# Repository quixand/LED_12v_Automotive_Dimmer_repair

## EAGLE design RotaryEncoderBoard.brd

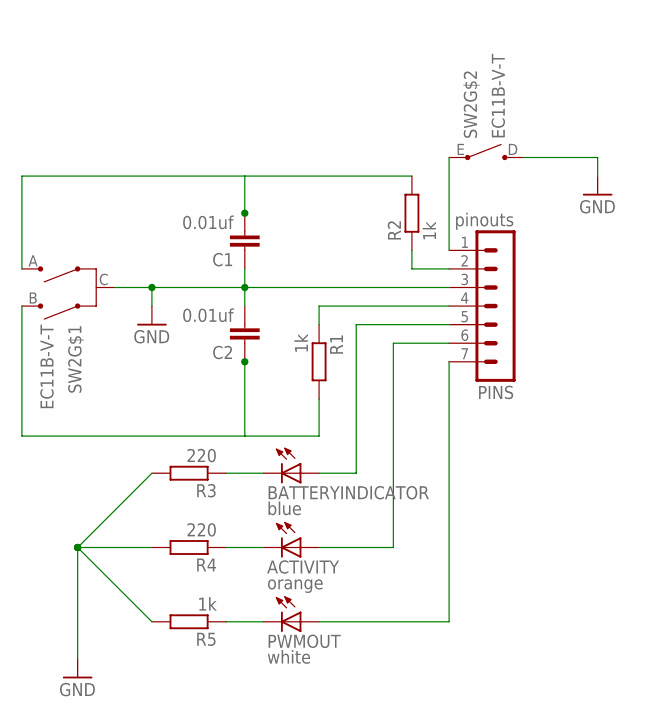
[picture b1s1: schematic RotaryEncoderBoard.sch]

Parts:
ACTIVITY: orange; LED-1206
BATTERYINDICATOR: blue; LED-1206
C1, C2: 0.01uf; C2.5-3
PINS: pinouts; MA07-1
PWMOUT: white; LED-1206
R1, R2, R5: 1k; 0204/7
R3, R4: 220; 0204/7
SW2: EC11B-V-T; EC11B-V

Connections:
GND: C1.1, C2.2, PINS.3, R3.2, R4.2, R5.2, SW2.C, SW2.D
unnamed: PINS.2, R2.1
unnamed: C1.2, R2.2, SW2.A
unnamed: C2.1, R1.2, SW2.B
unnamed: PINS.4, R1.1
unnamed: PINS.7, PWMOUT.A
unnamed: ACTIVITY.A, PINS.6
unnamed: PINS.1, SW2.E
unnamed: BATTERYINDICATOR.A, PINS.5
unnamed: PWMOUT.C, R5.1
unnamed: ACTIVITY.C, R4.1
unnamed: BATTERYINDICATOR.C, R3.1

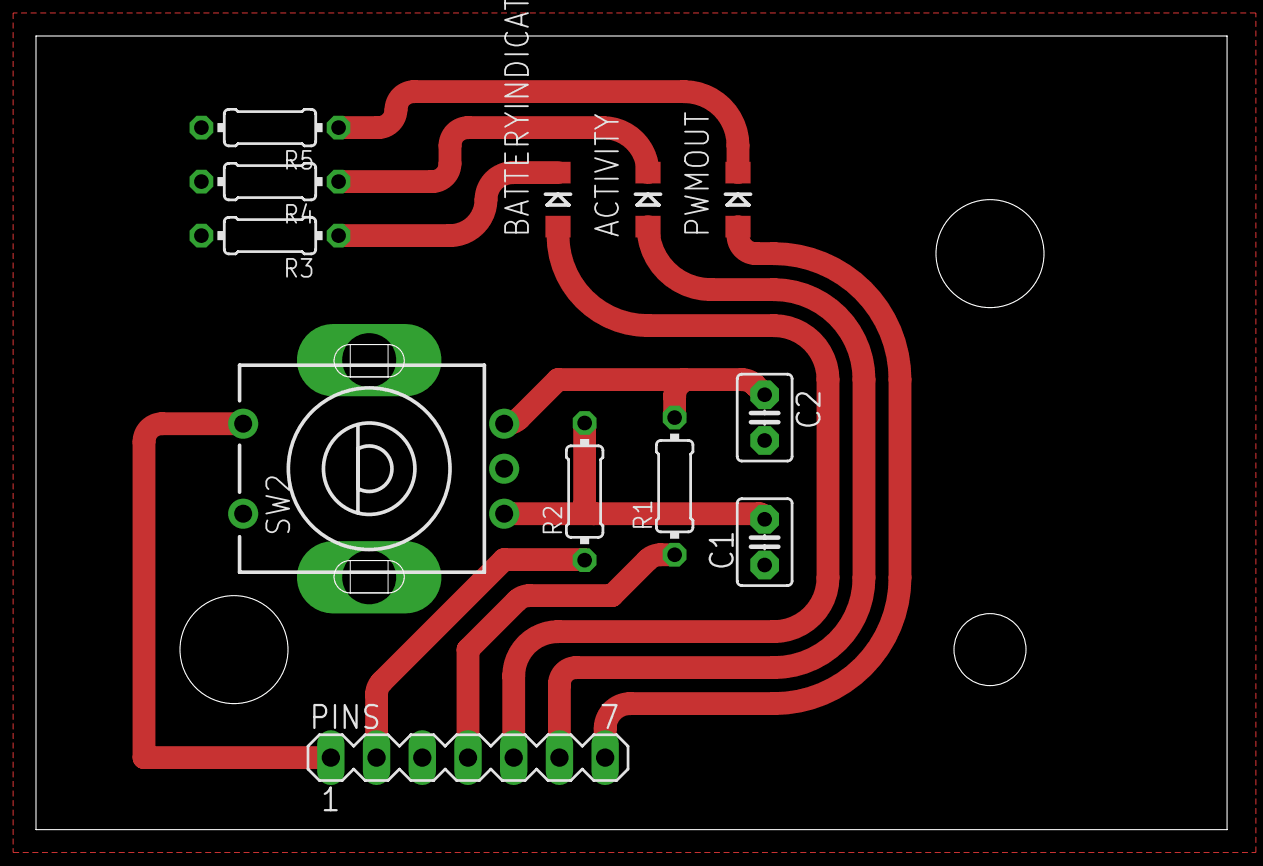
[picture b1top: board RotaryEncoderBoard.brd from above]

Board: 2 copper layers, 66.2 x 44.1 mm, 12 parts (0 on the bottom side), 12 nets.

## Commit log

2016-05-21 initial add for github
2016-05-21 tidying up some files, added gitignore
2016-05-21 adding remaining files
